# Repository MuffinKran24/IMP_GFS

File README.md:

# Mikrocontroller

Alle Dateien zu meiner GFS in Informatik.<br>

# Quellen
## Webquellen
- https://en.wikipedia.org/wiki/Microcontroller
- https://en.wikipedia.org/wiki/Microprocessor
- https://en.wikipedia.org/wiki/ATmega328#
- https://ww1.microchip.com/downloads/aemDocuments/documents/MCU08/ProductDocuments/DataSheets/ATmega48A-PA-88A-PA-168A-PA-328-P-DS-DS40002061B.pdf
- https://en.wikipedia.org/wiki/AVR_microcontrollers
- https://web.archive.org/web/20100217065617/http://smithsonianchips.si.edu/augarten/p38.htm
- https://historydraft.com/story/microprocessor/tms-1802nc/425/6336
- https://www.amd.com/en/products/processors/desktops/ryzen/9000-series/amd-ryzen-7-9850x3d.html
- https://en.wikipedia.org/wiki/Intel_4004
- https://en.wikipedia.org/wiki/RP2350
- https://en.wikipedia.org/wiki/Central_processing_unit#Structure_and_implementation
- https://de.wikipedia.org/wiki/Eingebettetes_System

## Bücher
- Taschenbuch Mikroprozessortechnik von Thomas Beierlein und Olaf Hagenbruch
- Mikrocontroller - Der Leitfaden für Maker von Klaus Dembowski

## Bilder
1. https://www.haase-cnc.de/thumbnail/7c/ce/95/1700311012/al1265profi_1000_1920x1920.jpg?ts=1700311019
2. https://www.robotlab.com/hubfs/NAO%20V6%20-%20TOP.png
3. https://dlcdnwebimgs.asus.com/gain/B742E991-0F43-40D0-8EA8-1D552222A976/w250/fwebp
4. https://bafnadevices.com/wp-content/uploads/2024/03/ATMEGA328P-AU.png
5. https://upload.wikimedia.org/wikipedia/commons/thumb/0/0c/ATMEGA328P-PU.jpg/500px-ATMEGA328P-PU.jpg
6. https://upload.wikimedia.org/wikipedia/commons/thumb/5/55/Intel_C4004.jpg/500px-Intel_C4004.jpg
7. https://upload.wikimedia.org/wikipedia/commons/thumb/6/6e/18MHZ_12MHZ_Crystal_110.jpg/500px-18MHZ_12MHZ_Crystal_110.jpg
(8. https://upload.wikimedia.org/wikipedia/commons/thumb/6/65/TI_TMS1000NLP_1a.jpg/500px-TI_TMS1000NLP_1a.jpg)
9. https://external-content.duckduckgo.com/iu/?u=https%3A%2F%2Fpreview.redd.it%2Feldorado-electrodata-8c-with-extremely-early-tms-1802-nc-v0-vz0gcc513cjb1.jpg%3Fwidth%3D4032%26format%3Dpjpg%26auto%3Dwebp%26s%3D216a5f173f79104319f0ad2b2162b1798d68cc4c&f=1&nofb=1&ipt=eab39682a445fb7439e256c5a7a231d153356b6771310c5e6803bdc67561d195
10. https://external-content.duckduckgo.com/iu/?u=https%3A%2F%2Fwww.electronicshub.org%2Fwp-content%2Fsmush-webp%2F2017%2F11%2FBasics-of-Microcontrollers-Image-1.jpg.webp&f=1&nofb=1&ipt=1901ea2dec7d194461aeedd058bc61d606a3ea7d56a901db18aa0892a35c1c40
11. https://overclockers.ru/st/r/800/-/legacy/blog/413830/714295_O.jpg
12. https://cdn-reichelt.de/bilder/web/artikel_ws/A300%2FRPI_RP2350B_NEW2025-07-30.jpg?type=Product&
13. https://upload.wikimedia.org/wikipedia/commons/thumb/3/3a/ABasicComputer.svg/960px-ABasicComputer.svg.png

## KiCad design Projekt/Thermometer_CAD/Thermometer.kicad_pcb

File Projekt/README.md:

# Ein einfaches Thermometer, das die Temperatur und Luftfeuchtigkeit auf einer Flüssigkristallanzeige anzeigt
## Bauteile:
- [Arduino UNO R3](https://www.conrad.de/de/p/arduino-a000066-board-uno-rev3-dil-core-atmega328-1275279.html)
- [LCD-1602A](https://www.amazon.de/AZDelivery-HD44780-Display-Zeichen-Arduino/dp/B08216WMDJ?tag=bingshoppin0b-21&linkCode=df0&hvadid=80127118566260&hvnetw=s&hvqmt=e&hvbmt=be&hvdev=c&hvlocint=undefined&hvlocphy=127417&hvtargid=pla-4583726587973319&th=1)
- [DHT11 Humidity & Temperature Sensor](https://www.conrad.de/de/p/joy-it-sen-ky015tf-temperatur-feuchtigkeitssensor-1-st-passend-fuer-entwicklungskits-arduino-1695379.html)
- [10K Potenziometer](https://www.conrad.de/de/p/piher-pt15nv02-103a2020-s-pt15nv02-103a2020-s-trimmer-linear-0-25-w-10-k-270-1-st-432024.html)

## Abhängigkeiten:
### Arduino IDE
- DHT sensor library (DHT Bibliothek)
- LiquidCrystal library (LCD Bibliothek)

### bare metal
- avrdude (Programm zum flashen des AVR-Chips auf dem Arduino)
- avr-gcc (C Compiler für den AVR-Chip)
- avr-libc (Standardbibliothek für den AVR-Chip)
- avr-binutils (Assembler für den AVR-Chip)
- make [(GNU/Linux exklusiv)](https://archlinux.org/download/)

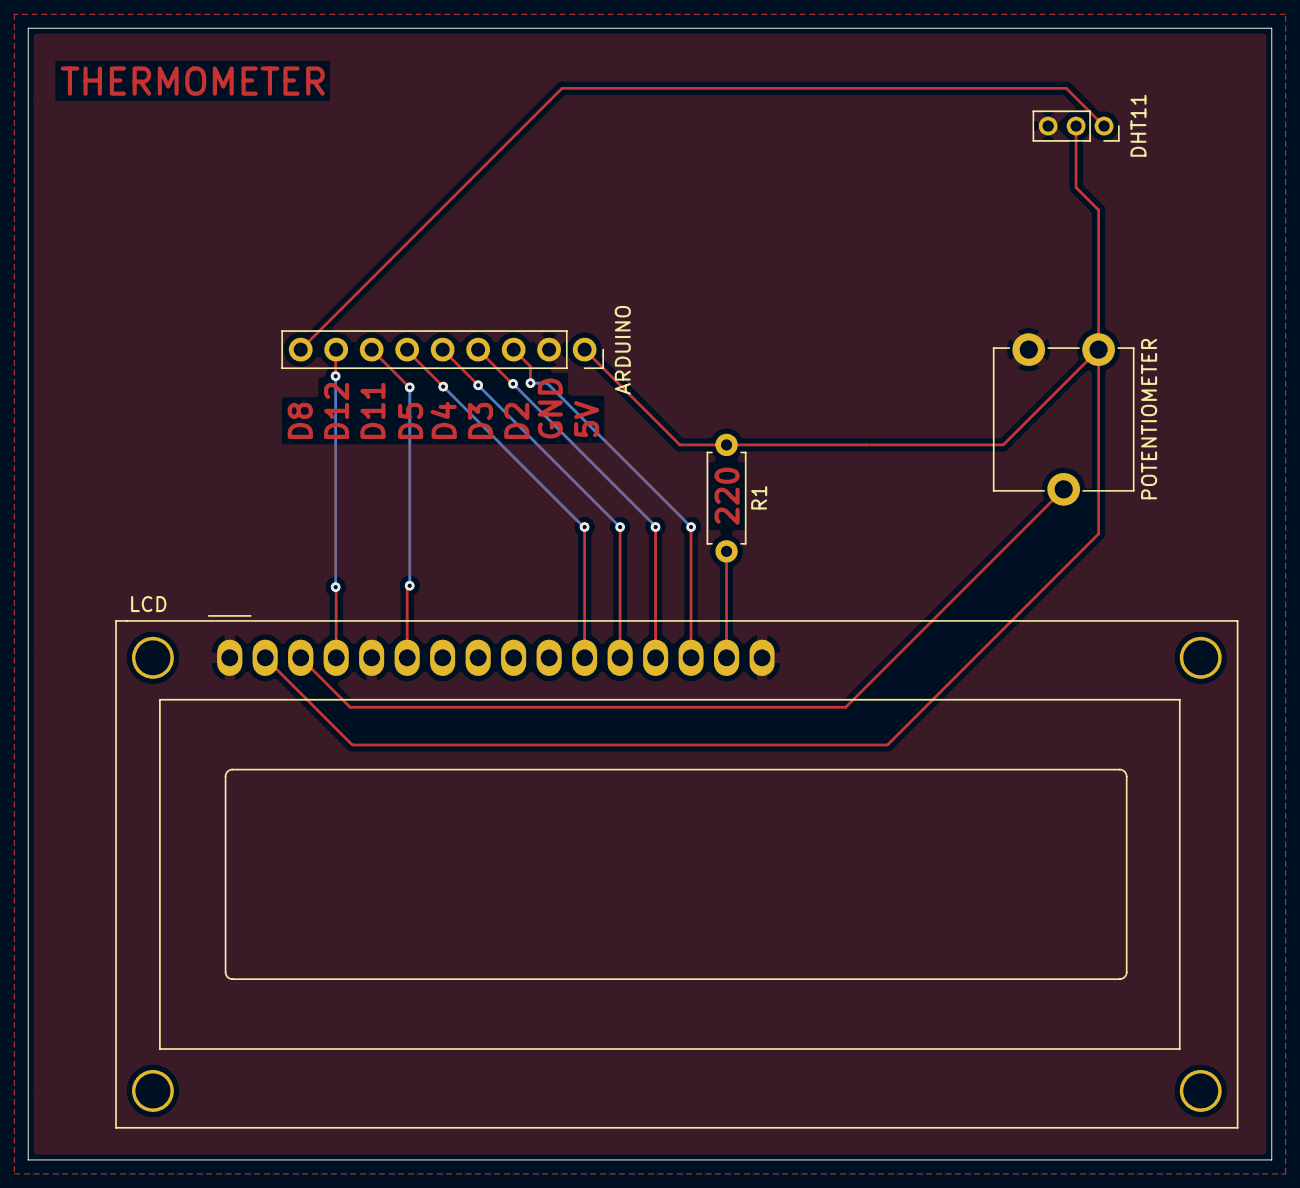
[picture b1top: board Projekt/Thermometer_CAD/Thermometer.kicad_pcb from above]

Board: 4 copper layers, 89.0 x 81.0 mm, 5 parts (0 on the bottom side), 11 nets.

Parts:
ARDUINO: Conn_01x09_Socket; PinSocket_1x09_P2.54mm_Vertical
DHT11: DHT11_Module; PinSocket_1x03_P2.00mm_Vertical
LCD: RC1602A; WC1602A
POTENTIOMETER: 10K; Potentiometer_ACP_CA9-V10_Vertical
R1: 220; R_Axial_DIN0207_L6.3mm_D2.5mm_P7.62mm_Horizontal

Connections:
+5V: ARDUINO.1, DHT11.2 (VCC), LCD.2 (VDD), POTENTIOMETER.3, R1.1
GND: ARDUINO.2, DHT11.3 (GND), LCD.1 (VSS), LCD.5 (R/W), LCD.16 (K), POTENTIOMETER.1
unnamed: ARDUINO.3, LCD.14 (DB7)
unnamed: ARDUINO.4, LCD.13 (DB6)
unnamed: ARDUINO.5, LCD.12 (DB5)
unnamed: ARDUINO.6, LCD.11 (DB4)
unnamed: ARDUINO.7, LCD.6 (E)
unnamed: ARDUINO.8, LCD.4 (RS)
unnamed: ARDUINO.9, DHT11.1 (DATA)
unnamed: LCD.15 (A/VEE), R1.2
unnamed: LCD.3 (VO), POTENTIOMETER.2

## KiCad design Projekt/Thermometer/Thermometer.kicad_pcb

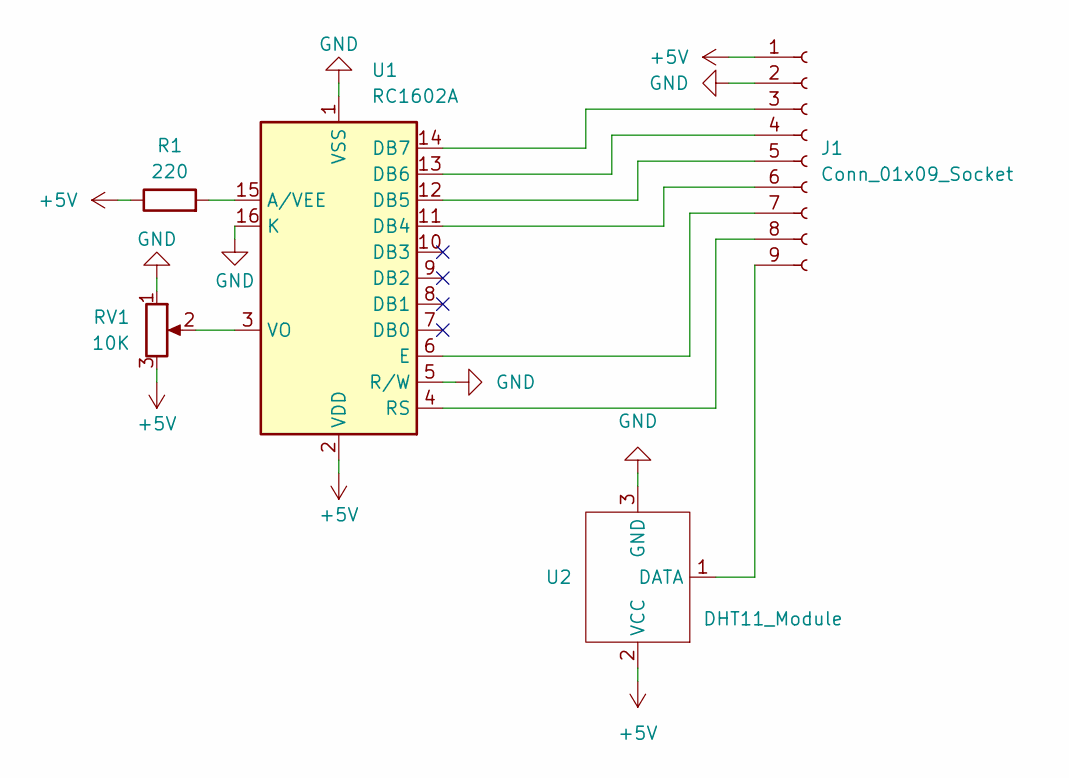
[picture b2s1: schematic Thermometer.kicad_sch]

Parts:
J1: Conn_01x09_Socket; PinSocket_1x09_P2.54mm_Vertical
R1: 220; R_Axial_DIN0207_L6.3mm_D2.5mm_P7.62mm_Horizontal
RV1: 10K; Potentiometer_ACP_CA9-V10_Vertical
U1: RC1602A; WC1602A
U2: DHT11_Module; PinSocket_1x03_P2.00mm_Vertical

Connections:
+5V: J1.1, R1.1, RV1.3, U1.2 (VDD), U2.2 (VCC)
GND: J1.2, RV1.1, U1.1 (VSS), U1.5 (R/W), U1.16 (K), U2.3 (GND)
unnamed: J1.3, U1.14 (DB7)
unnamed: J1.4, U1.13 (DB6)
unnamed: J1.5, U1.12 (DB5)
unnamed: J1.6, U1.11 (DB4)
unnamed: J1.7, U1.6 (E)
unnamed: J1.8, U1.4 (RS)
unnamed: J1.9, U2.1 (DATA)
unnamed: R1.2, U1.15 (A/VEE)
unnamed: RV1.2, U1.3 (VO)

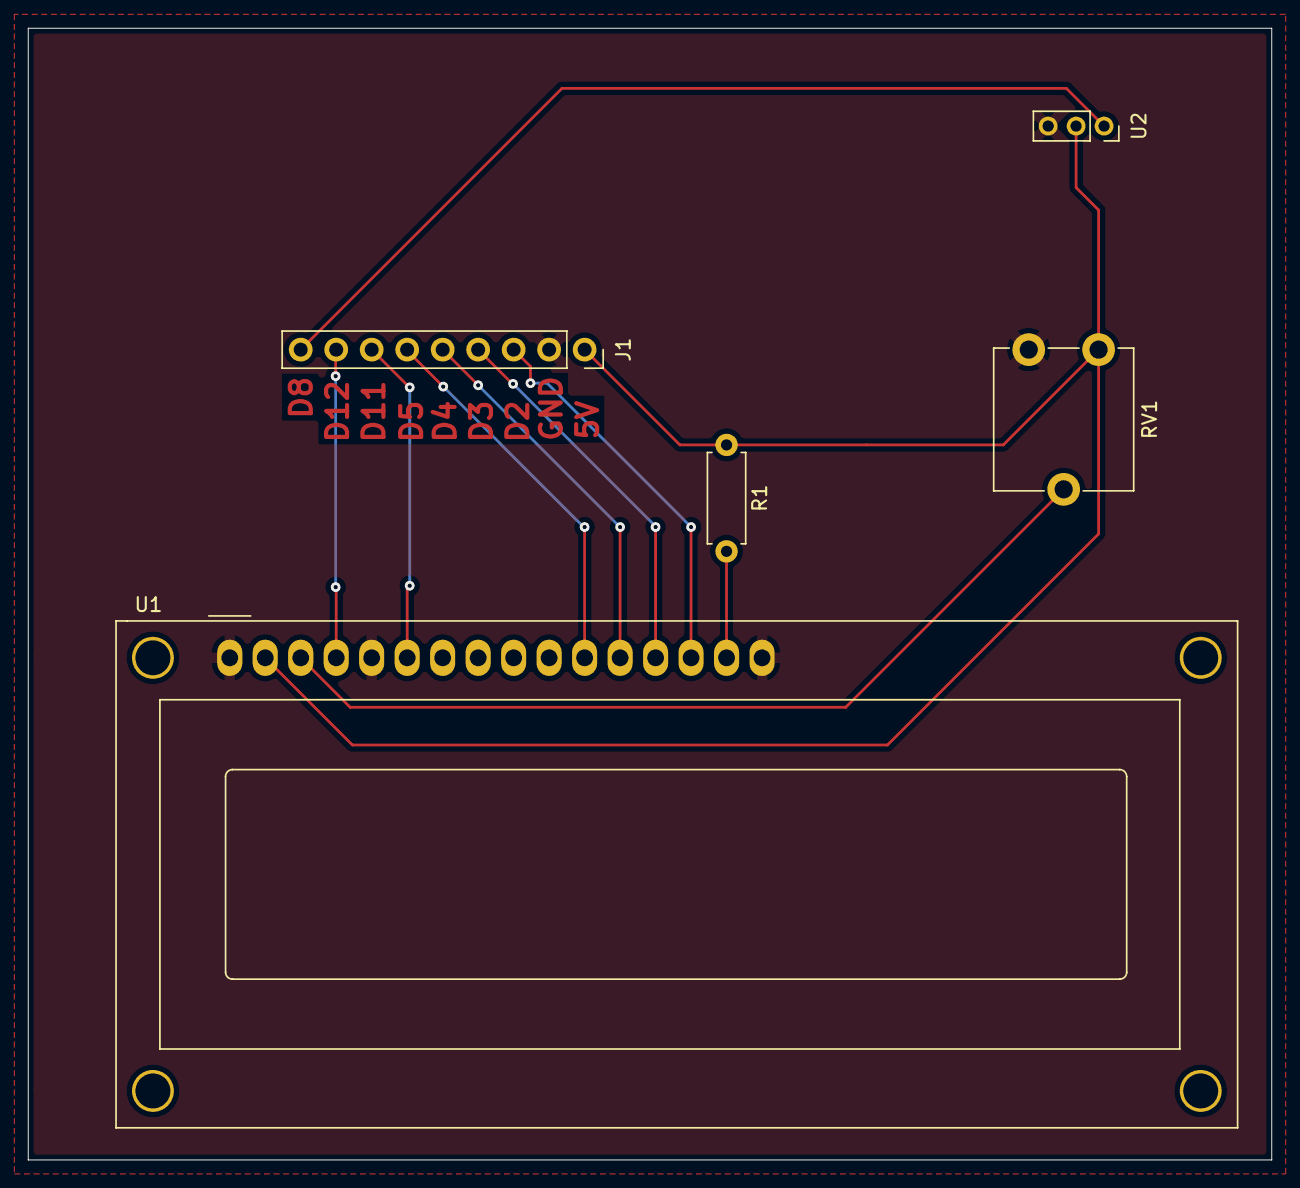
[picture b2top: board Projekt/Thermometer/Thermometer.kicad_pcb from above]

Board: 4 copper layers, 89.0 x 81.0 mm, 5 parts (0 on the bottom side), 11 nets.

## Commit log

2026-03-31 init
2026-03-31 präsentation
2026-03-31 last commit for this night
2026-04-03 wrote some comments for the project
2026-04-04 moved my notes here
2026-04-05 backup
2026-04-11 bare-metal blink example
2026-04-11 last commit for tonight
2026-04-16 backup_16-04-26
2026-04-17 literally no progress made today
2026-04-27 text
2026-04-27 fixed typo
2026-05-14 pcb layout
2026-05-19 no progress
2026-05-27 pause wegen 32°C in meinem zimmer
2026-05-27 schon wieder 1 uhr
2026-05-30 124356
2026-05-30 26754643643456754324567
2026-05-31 p-p-p-progress
2026-05-31 last commit for today
2026-06-05 progress has been made
2026-06-06 letzter commit im urlaub
2026-06-15 bald ist es soweit
2026-06-16 asdasdlöksdfgölsdhkjsdgflkgd
2026-06-17 handout
2026-06-18 letzter commit
2026-06-29 final final
